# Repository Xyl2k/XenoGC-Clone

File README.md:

# XenoGC-Clone
Board layout for http://www.gc-forever.com/wiki/index.php?title=XenoGC_Clone

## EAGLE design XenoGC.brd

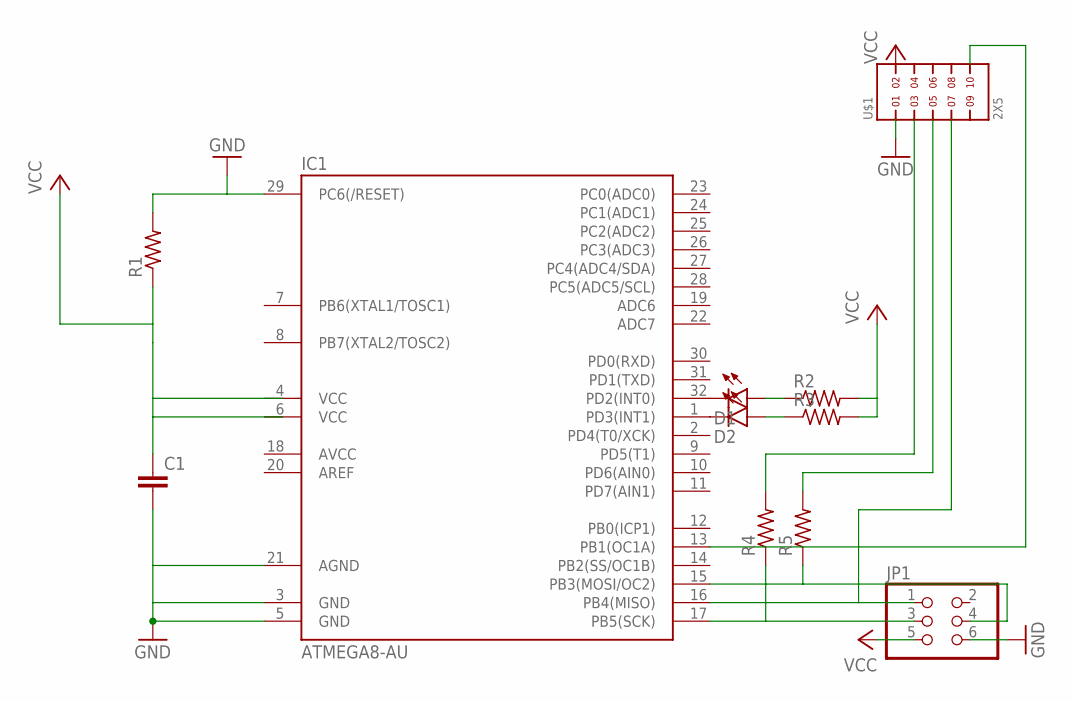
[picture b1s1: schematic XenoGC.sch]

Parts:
C1: C-EUC1206; C1206
D1, D2: PINK; LED-1206
IC1: ATMEGA8-AU; TQFP32-08
JP1: PINHD-2X3; 2X03
R1, R2, R3, R4, R5: R-US_R1206; R1206
U$1: 2X5; FTSH-105-01-XXX-DV-K

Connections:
GND: C1.2, IC1.3 (GND), IC1.5 (GND), IC1.21 (AGND), IC1.29 (PC6(/RESET)), JP1.6, R1.2, U$1.1
unnamed: D1.C, IC1.32 (PD2(INT0))
unnamed: D2.C, IC1.1 (PD3(INT1))
unnamed: D1.A, R2.1
unnamed: D2.A, R3.1
unnamed: IC1.17 (PB5(SCK)), JP1.3, R4.1
unnamed: IC1.16 (PB4(MISO)), JP1.1, U$1.7
unnamed: IC1.15 (PB3(MOSI/OC2)), JP1.4, R5.1
unnamed: R4.2, U$1.3
unnamed: R5.2, U$1.5
unnamed: IC1.13 (PB1(OC1A)), U$1.10
VCC: C1.1, IC1.4 (VCC), IC1.6 (VCC), JP1.5, R1.1, R2.2, R3.2, U$1.2

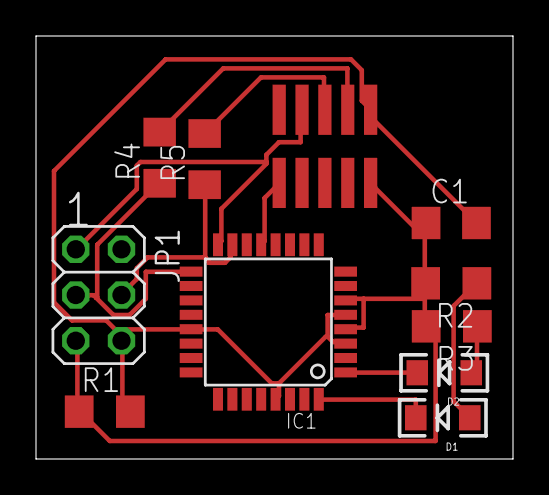
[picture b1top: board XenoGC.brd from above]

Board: 2 copper layers, 26.5 x 23.5 mm, 11 parts (0 on the bottom side), 12 nets.

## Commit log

2015-03-02 :boom::camel: Added .gitattributes & .gitignore files
2015-03-02 fimware
    fimware
2015-03-10 1.0
    1.0

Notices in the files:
parts and their libraries:
SparkFun-LED: Licensing: Creative Commons ShareAlike 4.0 International - https://creativecommons.org/licenses/by-sa/4.0
